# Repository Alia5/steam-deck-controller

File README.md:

# Steam Deck Standalone Controller

Convert your spare Steam Deck parts into a fully functional standalone controller! This project aims to repurpose original Steam Deck components into a custom-designed handheld controller.

This project is very much in its early stages, so please be patient as we work on developing the controller.  
We will be updating this README with more information as we progress.

## 🎯 Project Goals

- Create a standalone controller using original Steam Deck (LCD-Deck) parts
- Design and provide 3D printable shell (hopefully compatible with resin / FDM printers)
- Provide possibility for a basic wired-only controller build
- Implement wireless communication capabilities (TBD)

Additions like a chatpad, additional buttons, or other features are currently not the focus of the project  
as that would introduce additional complexity and require more custom parts.

Once wireless communication is implemented, we are open to exploring additional features, however.

## ✅ Current Progress

- [x] USB pinout reverse engineering completed ([details](./research/Controller_Boards.md))
- [x] Basic wired proof-of-concept showing the possibility ([demo video](https://youtu.be/daWLg8Y8ThU))
- [x] Design FFC to USB-C Breakout PCB ([details](./pcb-designs/ffc-usb-breakout))
  - For development purposes
  - [Optional] for wired-only controller builds
- [ ] Design 3D printable shell prototype (_Resin / FDM / SLS is TDB_)
- [ ] Develop firmware for wireless communication
- [ ] Create detailed assembly guide
- [ ] Design and test power management system
- [ ] TBD

## 🛜🔋 Wireless Approach

Our current approach for wireless functionality involves:

1. Custom MCU Board Design:
   - Acts as a USB-Host to the controller
   - Handles power management
   - Processes and forwards HID reports wirelessly

2. Custom USB Dongle:
   - Receives wireless signals from the controller
   - Emulates the original USB descriptors
   - Forwards HID reports to the computer

### 🤔 Why this approach?

- **Driver-Free Operation**: The USB dongle will emulate the original USB descriptors, allowing the controller to work without additional drivers.
- **No Additional Software**: The controller will work out-of-the-box via Steam.
- **No Firmware Modification**: The controller will work with the original Steam Deck firmware.

### ⚙️ Technical Considerations

- MCU chip selection
- Wireless protocol (considering 2.4GHz proprietary vs Bluetooth LE)
- Battery management

## 🛠️ Getting Started

[Coming Soon]

## 🗂️ Repository Structure

```dir
├── 3d-models/
├── pcb-designs/
│   └── ffc-usb-breakout/
├── firmware/
│   ├── controller-mcu/
│   └── dongle-mcu/
├── research/
└── media/
```

## 📋 Requirements

- Original Steam Deck controller parts (specific list coming soon)
- [Additional requirements TBD]

## 🤝 Contributing

Contributions are welcome! Please feel free to submit a Pull Request.

### 💬 Discord

Join our Discord server to discuss the project, ask questions, or share your ideas!  

## 📝 License

This project is licensed under the MIT License - see the [LICENSE](LICENSE) file for details.

## 🙏 Acknowledgments

- Steam Deck Controller Team
  - [Roni1993](https://github.com/Roni1993)
  - [Alia5](https://github.com/Alia5)
  - [oaSysFox](https://github.com/oaSysFox)
  - [Additional Members here]
- [Valve Corporation](https://www.valvesoftware.com/) - For creating the Steam Deck, the original Steam Controller and Steam Input
- [SlickBuys](slickbuysmodsandrepairs.com/) - For providing parts

## ⚠️ Disclaimer

This is a community project not affiliated with Valve Corporation. Use at your own risk.

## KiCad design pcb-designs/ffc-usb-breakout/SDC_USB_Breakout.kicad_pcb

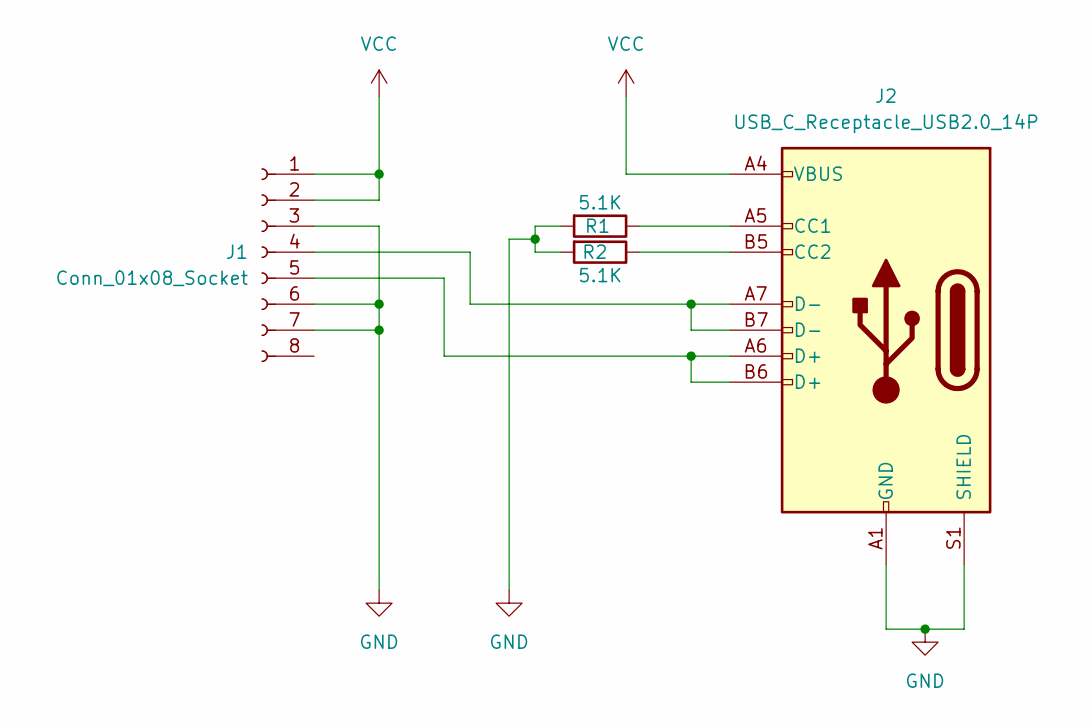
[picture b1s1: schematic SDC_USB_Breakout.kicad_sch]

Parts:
J1: Conn_01x08_Socket; Hirose_FH12-8S-0.5SH_1x08-1MP_P0.50mm_Horizontal; LCSC C262657
J2: USB_C_Receptacle_USB2.0_14P; USB_C_Receptacle_GCT_USB4105-xx-A_16P_TopMnt_Horizontal; LCSC C2936184
R1, R2: 5.1K; R_0603_1608Metric

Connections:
GND: J1.3, J1.6, J1.7, J2.A1 (GND), J2.A12 (GND), J2.B1 (GND), J2.B12 (GND), J2.S1 (SHIELD), R1.2, R2.2
unnamed: J1.4, J2.A7 (D-), J2.B7 (D-)
unnamed: J1.5, J2.A6 (D+), J2.B6 (D+)
unnamed: J2.A5 (CC1), R1.1
unnamed: J2.B5 (CC2), R2.1
VCC: J1.1, J1.2, J2.A4 (VBUS), J2.A9 (VBUS), J2.B4 (VBUS), J2.B9 (VBUS)

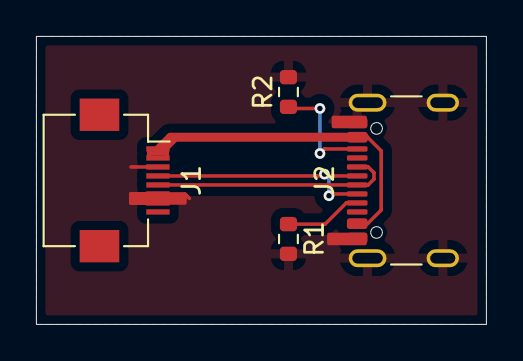
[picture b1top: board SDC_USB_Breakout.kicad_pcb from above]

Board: 2 copper layers, 25.0 x 16.0 mm, 4 parts (0 on the bottom side), 6 nets.

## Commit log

2024-10-05 First iteration FFC - USB-C breakout PCB
